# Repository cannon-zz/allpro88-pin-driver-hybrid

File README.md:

# KiCad Model of Logical Devices' ALLPRO88 Pin Driver Hybrid Module

## Overview

This provides a KiCad [schematic](https://github.com/user-attachments/files/18313998/pin_driver_hybrid.pdf) of the pin driver hybrid modules used in Logic Devices' ALLPRO88 software-driven device programmer.  The service manual scans available on the internet are missing the pages containing the pin driver circuitry.  I have traced out some of my own and guessed at what the SMD parts might be based on their markings and electrical properties.  I believe the schematic is correct, it's certainly correct enough for me to have repaired many of these modules based on what's here, but I found errors as recently as the fall of 2024 so I wouldn't say it's definitely correct.  Your mileage might vary.

The component reference designators are my own invention (there are no markings on the hybrid).  There is a PCB layout, but it's not meant to be used to make actual hybrid modules, it's only meant to help with debugging.  There are no traces or mounting pins.  Only the SMD components are placed in their approximate locations.  The resistors (which in the real hybrids are integrated directly into the traces) are mostly not placed properly at all.  Also, there are several revisions of the hybrid module, I have a mix of several in my own units myself, and the parts placement only matches one of them (I think the oldest version).  Good enough for me.

See also https://github.com/cannon-zz/allpro88-pin-driver.

## Service Suggestsions

Failures I've seen:

 * D1 and D2, the BYM13-30 reverse protection diodes for the TTL high output drivers, fail.  I've seen several do this.  When one of these fails, it becomes resistor-like when reverse biased, and provides a current path to ground backwards through the base-emitter junction of the NPN TTL high output drive transistor, and in through pin 7 of the HCT153.  Running current backwards through the transistor's base-emitter junction risks destroying it, but I've never seen any of them damaged by this failure.  Replacing the diode has always been sufficient to repair the fault.  Possibly the most clear symptom of this fault is a low output voltage when using the pull-up source.  Because of its high output impedance, that source is generally effective at detecting current paths to ground.

 * U7, the LM346M providing gain for the VDAC output drivers.  I saw several of these fail together on a group of pin driver boards.  I don't know why.  The symptom was that if ramping the VDAC output voltage it would be fine up to some threshold and then plateau, and could not be raised above that voltage.  The fault was isolated by confirming the voltage driving the hybrid was ramping properly, the output was not, and there was no significant voltage drop across the base resistor for the LM395P on the pin driver board (confirming no excessive load on the op amp's output).

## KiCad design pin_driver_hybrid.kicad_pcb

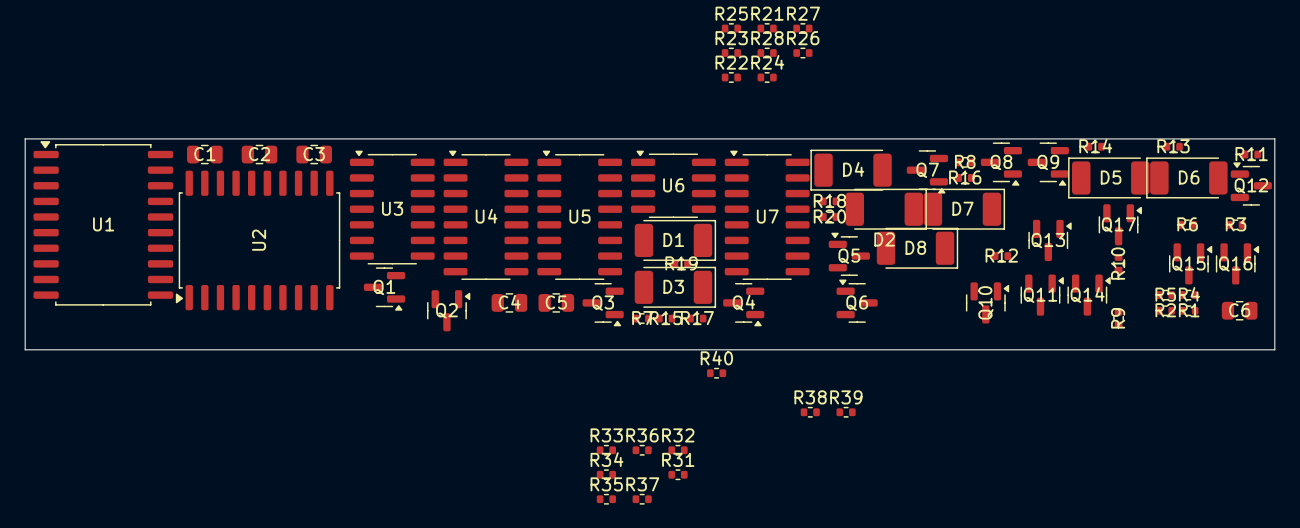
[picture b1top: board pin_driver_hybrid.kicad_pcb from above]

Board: 2 copper layers, 101.6 x 17.1 mm, 76 parts (0 on the bottom side), 85 nets, no tracks yet.

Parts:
C1, C2, C3, C4, C5, C6: C_Small; C_0805_2012Metric
D1, D2, D3, D4, D5, D6: BYM13-30; D_MELF
D7, D8: SM4001; D_MELF
Q1, Q2, Q8, Q9, Q10, Q11, Q12, Q13, Q14, Q15, Q16, Q17: MMBT2222AL; SOT-23
Q3, Q4, Q7: MMBT2907AL; SOT-23
Q5, Q6: BCW67C; SOT-23
R1, R4: 9.95k; R_0402_1005Metric
R2, R5: 100; R_0402_1005Metric
R3: 6.6; R_0402_1005Metric
R6: 8.4; R_0402_1005Metric
R7, R8, R15, R16: 10k; R_0402_1005Metric
R9, R10, R13, R14, R38, R39, R40: 1k; R_0402_1005Metric
R11, R12: 50; R_0402_1005Metric
R17, R18, R19, R20, R31, R32, R33, R34: 2.7k; R_0402_1005Metric
R21, R22, R23, R24: 2k; R_0402_1005Metric
R25, R26: 13k; R_0402_1005Metric
R27, R28: 5k; R_0402_1005Metric
R35, R36: 68; R_0402_1005Metric
R37: 100k; R_0402_1005Metric
U1, U2: 74HCT273; SOIC-20W_7.5x12.8mm_P1.27mm
U3: 7406; SOIC-14_3.9x8.7mm_P1.27mm
U4, U5: 74HCT153; SOIC-16_3.9x9.9mm_P1.27mm
U6: LM393; SOIC-8_3.9x4.9mm_P1.27mm
U7: LM346; SOIC-16_3.9x9.9mm_P1.27mm

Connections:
+5V: C1.1, C2.1, C3.1, C4.1, C5.1, R33.2, R34.2, U1.20 (VCC), U2.20 (VCC), U3.14 (VCC), U4.16 (VCC), U5.16 (VCC)
-5V: R9.1, R10.1, U7.13 (V-)
/DRV_{0}: Q10.3 (C), R25.2, R27.2
/DRV_{1}: Q11.3 (C), R26.1, R28.2
/D_{0}: U1.3 (D0), U2.3 (D0)
/D_{1}: U1.4 (D1), U2.4 (D1)
/D_{2}: U1.7 (D2), U2.7 (D2)
/D_{3}: U1.8 (D3), U2.8 (D3)
/D_{4}: U1.13 (D4), U2.13 (D4)
/D_{5}: U1.14 (D5), U2.14 (D5)
/D_{6}: U1.17 (D6), U2.17 (D6)
/D_{7}: U1.18 (D7), U2.18 (D7)
/OUT_{0}: D1.1 (K), D7.1 (K), R11.1, R17.1, U6.5 (+)
/OUT_{1}: D2.1 (K), D8.1 (K), R12.1, R18.1, U6.3 (+)
/PD_EN_{0}: U1.19 (Q7), U3.13
/PD_EN_{1}: U2.19 (Q7), U3.11
/PU_EN_{0}: U1.12 (Q4), U3.1
/PU_EN_{1}: U2.12 (Q4), U3.9
/TTL_CLK_EN_{0}: U1.16 (Q6), U4.2 (S1)
/TTL_CLK_EN_{1}: U2.16 (Q6), U5.2 (S1)
/TTL_HI_EN_{0}: U1.9 (Q3), U4.5 (I1a), U4.6 (I0a)
/TTL_HI_EN_{1}: U2.9 (Q3), U5.5 (I1a), U5.6 (I0a)
/TTL_LO_EN_{0}: U1.15 (Q5), U4.10 (I0b), U4.11 (I1b), U4.14 (S0)
/TTL_LO_EN_{1}: U2.15 (Q5), U5.10 (I0b), U5.11 (I1b), U5.14 (S0)
/VDAC_EN_{0}: U1.5 (Q1), U3.3
/VDAC_EN_{1}: U2.5 (Q1), U3.5
/VTST_EN_{0}: R31.1, U1.6 (Q2)
/VTST_EN_{1}: R32.1, U2.6 (Q2)
/V_{ADJ}: U6.8 (V+), U7.4 (V+)
/V_{PU}: Q3.2 (E), Q7.2 (E), R7.2, R8.2
/V_{TH}: U6.2 (-), U6.6 (-)
/V_{TST}: Q5.2 (E), Q6.2 (E), R38.2, R39.2
/V_{TTL}: C6.1, Q15.3 (C), Q16.3 (C), R1.2, R4.2
/~RESET: U1.1 (~Mr), U2.1 (~Mr)
/ϕ_{0}: U4.4 (I2a), U4.13 (I3b), U5.4 (I2a), U5.13 (I3b)
/ϕ_{1}: U4.3 (I3a), U4.12 (I2b), U5.3 (I3a), U5.12 (I2b)
GNDA: Q4.1 (B), R23.2, R24.2, U7.12 (+), U7.14 (+)
GNDD: C1.2, C2.2, C3.2, C4.2, C5.2, C6.2, Q1.2 (E), Q9.2 (E), Q10.2 (E), Q11.2 (E), Q12.2 (E), Q13.2 (E), Q14.1 (B), Q17.1 (B), R35.2, R36.2, U1.10 (GND), U2.10 (GND), U3.7 (GND), U4.1 (Ea), U4.8 (GND), U4.15 (Eb), U5.1 (Ea), U5.8 (GND), U5.15 (Eb), U6.4 (V-)
unnamed: D1.2 (A), R3.2
unnamed: D2.2 (A), R6.2
unnamed: D3.2 (A), Q3.3 (C)
unnamed: D3.1 (K), R17.2, R19.1
unnamed: D4.2 (A), Q7.3 (C)
unnamed: D4.1 (K), R18.2, R20.1
unnamed: D5.2 (A), Q13.1 (B), R14.2
unnamed: D5.1 (K), R14.1, U5.9 (Zb)
unnamed: D6.2 (A), Q12.1 (B), R13.2
unnamed: D6.1 (K), R13.1, U4.9 (Zb)
unnamed: D7.2 (A), Q5.3 (C)
unnamed: D8.2 (A), Q6.3 (C)
unnamed: Q1.1 (B), Q2.2 (E), R36.1
unnamed: Q1.3 (C), Q2.1 (B), R32.2
unnamed: Q2.3 (C), Q6.1 (B), R39.1
unnamed: Q3.1 (B), R7.1, R15.2
unnamed: Q4.3 (C), R40.2
unnamed: Q4.2 (E), R37.2
unnamed: Q5.1 (B), Q8.3 (C), R38.1
unnamed: Q7.1 (B), R8.1, R16.2
unnamed: Q8.1 (B), Q9.3 (C), R31.2
unnamed: Q8.2 (E), Q9.1 (B), R35.1
unnamed: Q10.1 (B), R33.1, U3.4
unnamed: Q11.1 (B), R34.1, U3.6
unnamed: Q12.3 (C), R11.2
unnamed: Q13.3 (C), R12.2
unnamed: Q14.2 (E), R9.2
unnamed: Q15.1 (B), R5.2
unnamed: Q15.2 (E), R6.1
unnamed: Q16.1 (B), R2.2
unnamed: Q16.2 (E), R3.1
unnamed: Q17.2 (E), R10.2
unnamed: R15.1, U3.2
unnamed: R16.1, U3.8
unnamed: R19.2, U3.12
unnamed: R20.2, U3.10
unnamed: R27.1, U7.1
unnamed: R28.1, U7.7
unnamed: R1.1, R2.1, U4.7 (Za)
unnamed: R4.1, R5.1, U5.7 (Za)
unnamed: R21.1, U7.3 (+)
unnamed: R23.1, R25.1, U7.2 (-)
unnamed: R40.1, U7.8 (SET)
unnamed: R22.1, U7.5 (+)
unnamed: R24.1, R26.2, U7.6 (-)
unnamed: U7.10, U7.11 (-)
unnamed: U7.15 (-), U7.16

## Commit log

2025-01-06 add README.md
2025-01-06 README.md: add reference to pin driver schematic
2025-01-06 README.md: add link to .pdf
2025-01-06 README.md: add service notes
